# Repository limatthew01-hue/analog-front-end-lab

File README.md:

# Analog front-end lab

A simulation of a low-voltage sensor input: a 10 kΩ / 10 nF RC filter, 1.65 V bias, and an ideal 12-bit ADC with a 3.3 V reference. The goal is to preserve a 100 Hz signal while reducing a separate 20 kHz interference tone, then examine component tolerance and quantization.

This is a completed simulation study, not a fabricated circuit or a hardware measurement. Python provides the equations, waveforms, tolerance study, and ADC model. ngspice independently checks the RC response.

## Run

Use Python 3.10 or newer. From the repository root:

```sh
python3 -m venv .venv
source .venv/bin/activate
python -m pip install -r requirements.txt
python -m unittest discover -s tests -v
python src/front_end.py --out results/python
```

Windows activation: `.venv\Scripts\activate`. Only NumPy and Matplotlib are required for the Python analysis.

To regenerate the committed results, also install [ngspice](https://ngspice.sourceforge.io/download.html) and make it available on PATH:

```sh
python src/front_end.py --out results --spice
```

Use `--ngspice /path/to/ngspice` if necessary. This runs AC and transient checks and returns an error if they exceed the declared tolerances. `make test`, `make run`, and `make spice` provide the same entry points.

## Nominal results

The synthetic input is 1.65 V plus a 100 mV-peak, 100 Hz sine and a 40 mV-peak, 20 kHz sine. The ADC samples at 200 ksample/s. The run lasts 30 ms; the first 10 ms are excluded from waveform error and ratio calculations.

| Quantity | Result |
| --- | ---: |
| RC cutoff | 1,591.549 Hz |
| Gain at 100 Hz | 0.998032 V/V |
| Gain at 20 kHz | 0.079327 V/V |
| Input signal/interference ratio | 7.959 dB |
| Filtered signal/interference ratio | 29.953 dB |
| Signal/total error after ideal ADC | 29.906 dB |
| ADC LSB | 805.664 µV |
| ADC reconstruction error RMS | 230.615 µV |
| Analog output range | 1.5470–1.7530 V |
| ADC clipping | 0 of 6,000 samples |

The ratio improvement is about 22 dB for these two tones. It is not broadband SNR, ENOB, or proof that the circuit is a sufficient anti-alias filter for a real ADC.

The open markers are ngspice AC results; the green curve is the RC equation. For the recorded ngspice 42 run, all 401 frequency points pass a relative complex-error tolerance of 1e-6. The actual maximum is approximately 9.81e-16. The transient check differs from the analytical output by at most 1.267 µV after the measurement start, below the 10 µV threshold. This agreement checks the ideal circuit model, not real component accuracy.

## Equations and ADC convention

The unloaded filter uses `H(jω) = 1 / (1 + jωRC)` and `fc = 1 / (2πRC)`. The time-domain response is the exact sine response plus its decaying initial-condition term. The capacitor begins at the 1.65 V DC bias. There is no Euler time-step approximation in the Python waveform model.

The ideal ADC has `2^12 = 4096` bins of width `3.3 / 4096 V`. Each input maps to its lower-bin code, clamped to 0–4095, and is reconstructed at the center of that bin. The nonclipped reconstruction error is bounded by half an LSB. Values below 0 V or at/above 3.3 V are flagged as clipped.

The RC resistor's ideal equilibrium thermal estimate, `sqrt(kT/C)`, is 0.644 µV RMS at 300 K. The usual uniform-error ADC estimate, `LSB/sqrt(12)`, is 232.575 µV RMS. These are analytical estimates; thermal noise is not injected into the plotted waveform, and the deterministic ADC error need not be perfectly uniform.

## Component variation

The study draws 10,000 independent component sets with uniform R ±1% and C ±5% variation, using seed 7. The 5th–95th cutoff percentiles are 1,521.85–1,666.93 Hz. Deterministic worst-case corners are 1,500.75–1,692.24 Hz. These bounds describe the chosen tolerance model, not measured production data or a confidence interval for actual devices.

## Files

- `src/front_end.py`: equations, waveform and ADC models, tolerance study, CLI, and SPICE cross-check.
- `spice/rc_ac.cir`: nominal AC netlist.
- `spice/rc_transient.cir`: nominal biased sensor and interference netlist.
- `tests/test_front_end.py`: 19 tests.
- `results/metrics.json`: exact configuration and recorded numerical results.
- `results/frequency_response.csv`: 401-point AC response.
- `results/waveforms.csv`: all 6,000 simulated ADC samples.
- `results/spice_ac_check.csv`: theory and independent SPICE values at the same frequencies.
- `results/cutoff_distribution.csv`: histogram bins for the tolerance sweep.
- `results/report.md`: generated report.

The large raw ngspice transient output is regenerated in ignored `build/`, rather than committed. To run the nominal netlists directly:

```sh
mkdir -p build
ngspice -b spice/rc_ac.cir
ngspice -b spice/rc_transient.cir
```

The generated netlists in `build/` use the current CLI parameters. The checked-in `spice/` copies use the nominal component values.

## Verification and limits

The tests check DC gain, the -3.0103 dB / -45° cutoff, high-frequency roll-off, finite-load behavior, initial conditions, the RC differential equation via an independent numerical derivative, ADC bins and half-LSB error bounds, tolerance corners, reproducible seeds, and time-domain versus frequency-domain tone ratios.

The main simulation assumes an ideal source, ideal bias, and infinite ADC input impedance. A finite resistive load changes both gain and cutoff; a real ADC's switched sampling capacitor is more complicated still. Reference noise, amplifier behavior, INL/DNL, aperture jitter, parasitics, and physical anti-alias performance are excluded. A hardware extension needs a chosen ADC, acquisition/settling analysis, real bias circuitry, and measured waveforms before making board-level claims.

## Related machine-learning project

[Sensor Signal Classifier](projects/sensor-signal-classifier/) is a separate personal project in this repository. It compares fixed rules, logistic regression, and a random forest on simulated ADC signal conditions, with device-disjoint splits and a noise stress test. Its code, setup instructions, and results are self-contained in that folder.

## Related motor-control project

[Zybo Motor Speed Controller](projects/zybo-motor-controller/) implements encoder feedback, fixed-point PI control, 20 kHz PWM, a CRC-protected serial link, and a Python operator panel. It includes a switched-PWM motor simulation, self-checking RTL tests, and a hardware wiring guide. Physical board and motor measurements are pending. This project is self-contained in its own folder.

## PCB and embedded firmware

[Dual-Channel Sensor Interface PCB](projects/sensor-interface-pcb/) contains an editable KiCad schematic and routed two-layer board, BOM, fabrication exports, netlist comparison and native DRC report. [Bare-Metal STM32 Sensor Logger](projects/bare-metal-stm32-logger/) implements timer-triggered ADC sampling, circular DMA, UART queues and CRC-protected telemetry in C. Both are prototype projects; fabrication and physical MCU testing are pending.

## References

- [Texas Instruments: low-pass filtered non-inverting amplifier](https://www.ti.com/tool/CIRCUIT060057): background on an RC input pole. This lab models the passive RC portion only, not TI's amplifier circuit.
- [ngspice documentation](https://ngspice.sourceforge.io/docs.html): AC and transient simulation and control commands.

[Matthew Li's engineering portfolio](https://matthew-li-portfolio.li-matthew01.chatgpt.site)

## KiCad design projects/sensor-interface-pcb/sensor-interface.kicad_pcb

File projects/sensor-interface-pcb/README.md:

# Dual-channel sensor interface PCB

A 60 × 40 mm, two-layer board for connecting two slow, positive voltage signals to a NUCLEO-F401RE. Each channel has a 2:1 resistor divider, an MCP6002 voltage follower, and a 10 kΩ / 1 µF output filter. The MCU stays on the Nucleo board; a four-wire harness carries power, ground and the two ADC inputs.

**Revision A is a CAD prototype.** It has not been fabricated, assembled or measured. KiCad checks and an ideal-buffer simulation are complete; they do not establish hardware performance or production readiness.

## Circuit choices

The intended input range is 0–6 V with the interface powered from regulated 3.3 V. Two 33 kΩ, 1% resistors load each input by 66 kΩ and produce half the input voltage. At 6 V, the nominal buffer input is 3.0 V. The MCP6002 runs from 3.3 V; both amplifiers are unity-gain followers. The 10 kΩ resistor isolates the amplifier from the 1 µF ADC-side capacitor. C1 is the local 100 nF bypass, and C4 adds 4.7 µF near the harness.

The nominal RC cutoff is `1 / (2π × 10000 × 1e-6) = 15.915 Hz`. This design is intended for signals below roughly 5 Hz. A single RC pole is not a guarantee of alias rejection for arbitrary interference at the 100 Hz acquisition rate.

The 1% divider corners are 0.495–0.505 V/V. Assuming R ±1% and effective C ±10%, the cutoff corners are 14.325–17.863 Hz. Actual ceramic capacitance can change with DC bias and temperature; select a part whose effective capacitance meets the design target. These calculations exclude op-amp offset/noise, ADC reference error, switched-capacitor loading and layout parasitics.

## Connection to the Nucleo

J1 is a **wired harness**, not an Arduino shield footprint. Read the pin-1 square pad and silkscreen before connecting it.

| PCB pin | Signal | NUCLEO-F401RE connection |
| --- | --- | --- |
| J1.1 | +3V3 | CN6.4, 3.3 V output |
| J1.2 | GND | CN6.6, ground |
| J1.3 | ADC0 | CN8.1, A0 / PA0 / ADC1 channel 0 |
| J1.4 | ADC1 | CN8.2, A1 / PA1 / ADC1 channel 1 |
| J2.1 / J2.2 | Input 0 / ground | External 0–6 V signal / common ground |
| J3.1 / J3.2 | Input 1 / ground | External 0–6 V signal / common ground |

Supply this board from **3.3 V**, and disconnect external signals when its power is off. There is no reverse-polarity protection, isolation or overvoltage clamp; the divider is a scaling network, not a protected industrial input.

The matching [bare-metal STM32 logger](../bare-metal-stm32-logger/) configures these ADC channels and sends CRC-protected records through the Nucleo's ST-LINK virtual COM port.

## CAD and checks

Open `sensor-interface.kicad_pro` in **KiCad 7 or newer**. The schematic embeds its symbols. The PCB embeds its footprint geometry and also references the standard KiCad footprint libraries through `fp-lib-table`. On KiCad versions with a different library environment name, set `KICAD7_FOOTPRINT_DIR` to your installed footprint directory or update that table.

Recorded KiCad 7.0.11 results:

| Check | Result |
| --- | --- |
| Physical/electrical DRC | 0 violations |
| Unconnected pads | 0 |
| Footprint errors | 0 |
| Schematic-to-board net membership | All 36 pin connections across 10 nets match |
| Layout | 0.25 mm tracks; eight 0.6 / 0.3 mm vias; four 3.2 mm mounting holes |

`results/drc.txt` is the native KiCad report. `results/verification.json` records the independent netlist comparison. **ERC was not run**: the installed KiCad 7 CLI has no ERC command. Run ERC in the schematic editor and review the schematic and footprints before ordering. Zero DRC errors do not prove the circuit works.

On a Linux KiCad installation whose Python can import `pcbnew`:

```sh
make check
make export
# Optional regeneration from design.json; this replaces manual layout edits:
make regenerate
make check
make export
```

`design.json` is the generator's component/pin manifest. `scripts/build_board.py` places standard footprints, routes both layers and fills the back ground plane. The editable `.kicad_pcb` is the board used for the recorded DRC and exports. After manual CAD edits, use `make check` and `make export`, not `make regenerate`.

## Analog model

```sh
python3 -m venv .venv
. .venv/bin/activate
python -m pip install -r requirements.txt
python scripts/analyze.py --ngspice ngspice
```

The 401-point ngspice AC check uses an **ideal voltage-controlled buffer**, not an MCP6002 device model. It agrees with the analytical divider-plus-RC response to a maximum complex error of about `1.3e-9 V/V`. See `results/analog.json`, `results/frequency.csv` and the generated plot. This validates the passive calculation only.

## Fabrication package and bring-up

`fabrication/` contains the copper, solder mask, paste, silkscreen, board outline and metric Excellon drill export. The drill file declares plated vias, plated header holes and nonplated mounting holes separately in its tool attributes. `bom.csv` lists values, ratings and footprints; select exact passive parts and check their dimensions and capacitor derating before assembly. The U1 package is SOIC-8, **MCP6002-I/SN**.

The first physical checks are still pending:

1. Run schematic ERC and review the generated fabrication layers, drill plating and component orientation.
2. Inspect for shorts, then power from a current-limited 3.3 V source with signal sources disconnected. Check U1 pins 8 and 4.
3. Apply known, common-ground DC voltages to one input at a time. Measure the divider, buffer and ADC nodes before connecting the MCU.
4. Flash the companion firmware, enter the measured ADC reference voltage, and compare stable readings against a DMM.
5. Scope a slow input step and the ADC node. Check settling, reference noise and stability with the actual selected capacitors and wiring.

## Sources

- [Microchip MCP6001/2/4 datasheet, DS20001733L](https://ww1.microchip.com/downloads/en/DeviceDoc/MCP6001-1R-1U-2-4-1-MHz-Low-Power-Op-Amp-DS20001733L.pdf): package pins, supply range and amplifier characteristics.
- [ST Nucleo-64 manual, UM1724](https://www.st.com/resource/en/user_manual/um1724-stm32-nucleo64-boards-mb1136-stmicroelectronics.pdf): F401RE connector mappings.
- [ST STM32F401RE datasheet](https://www.st.com/resource/en/datasheet/stm32f401re.pdf): ADC and device electrical characteristics.
- [KiCad library license](https://www.kicad.org/libraries/license/): standard footprint attribution and exception.

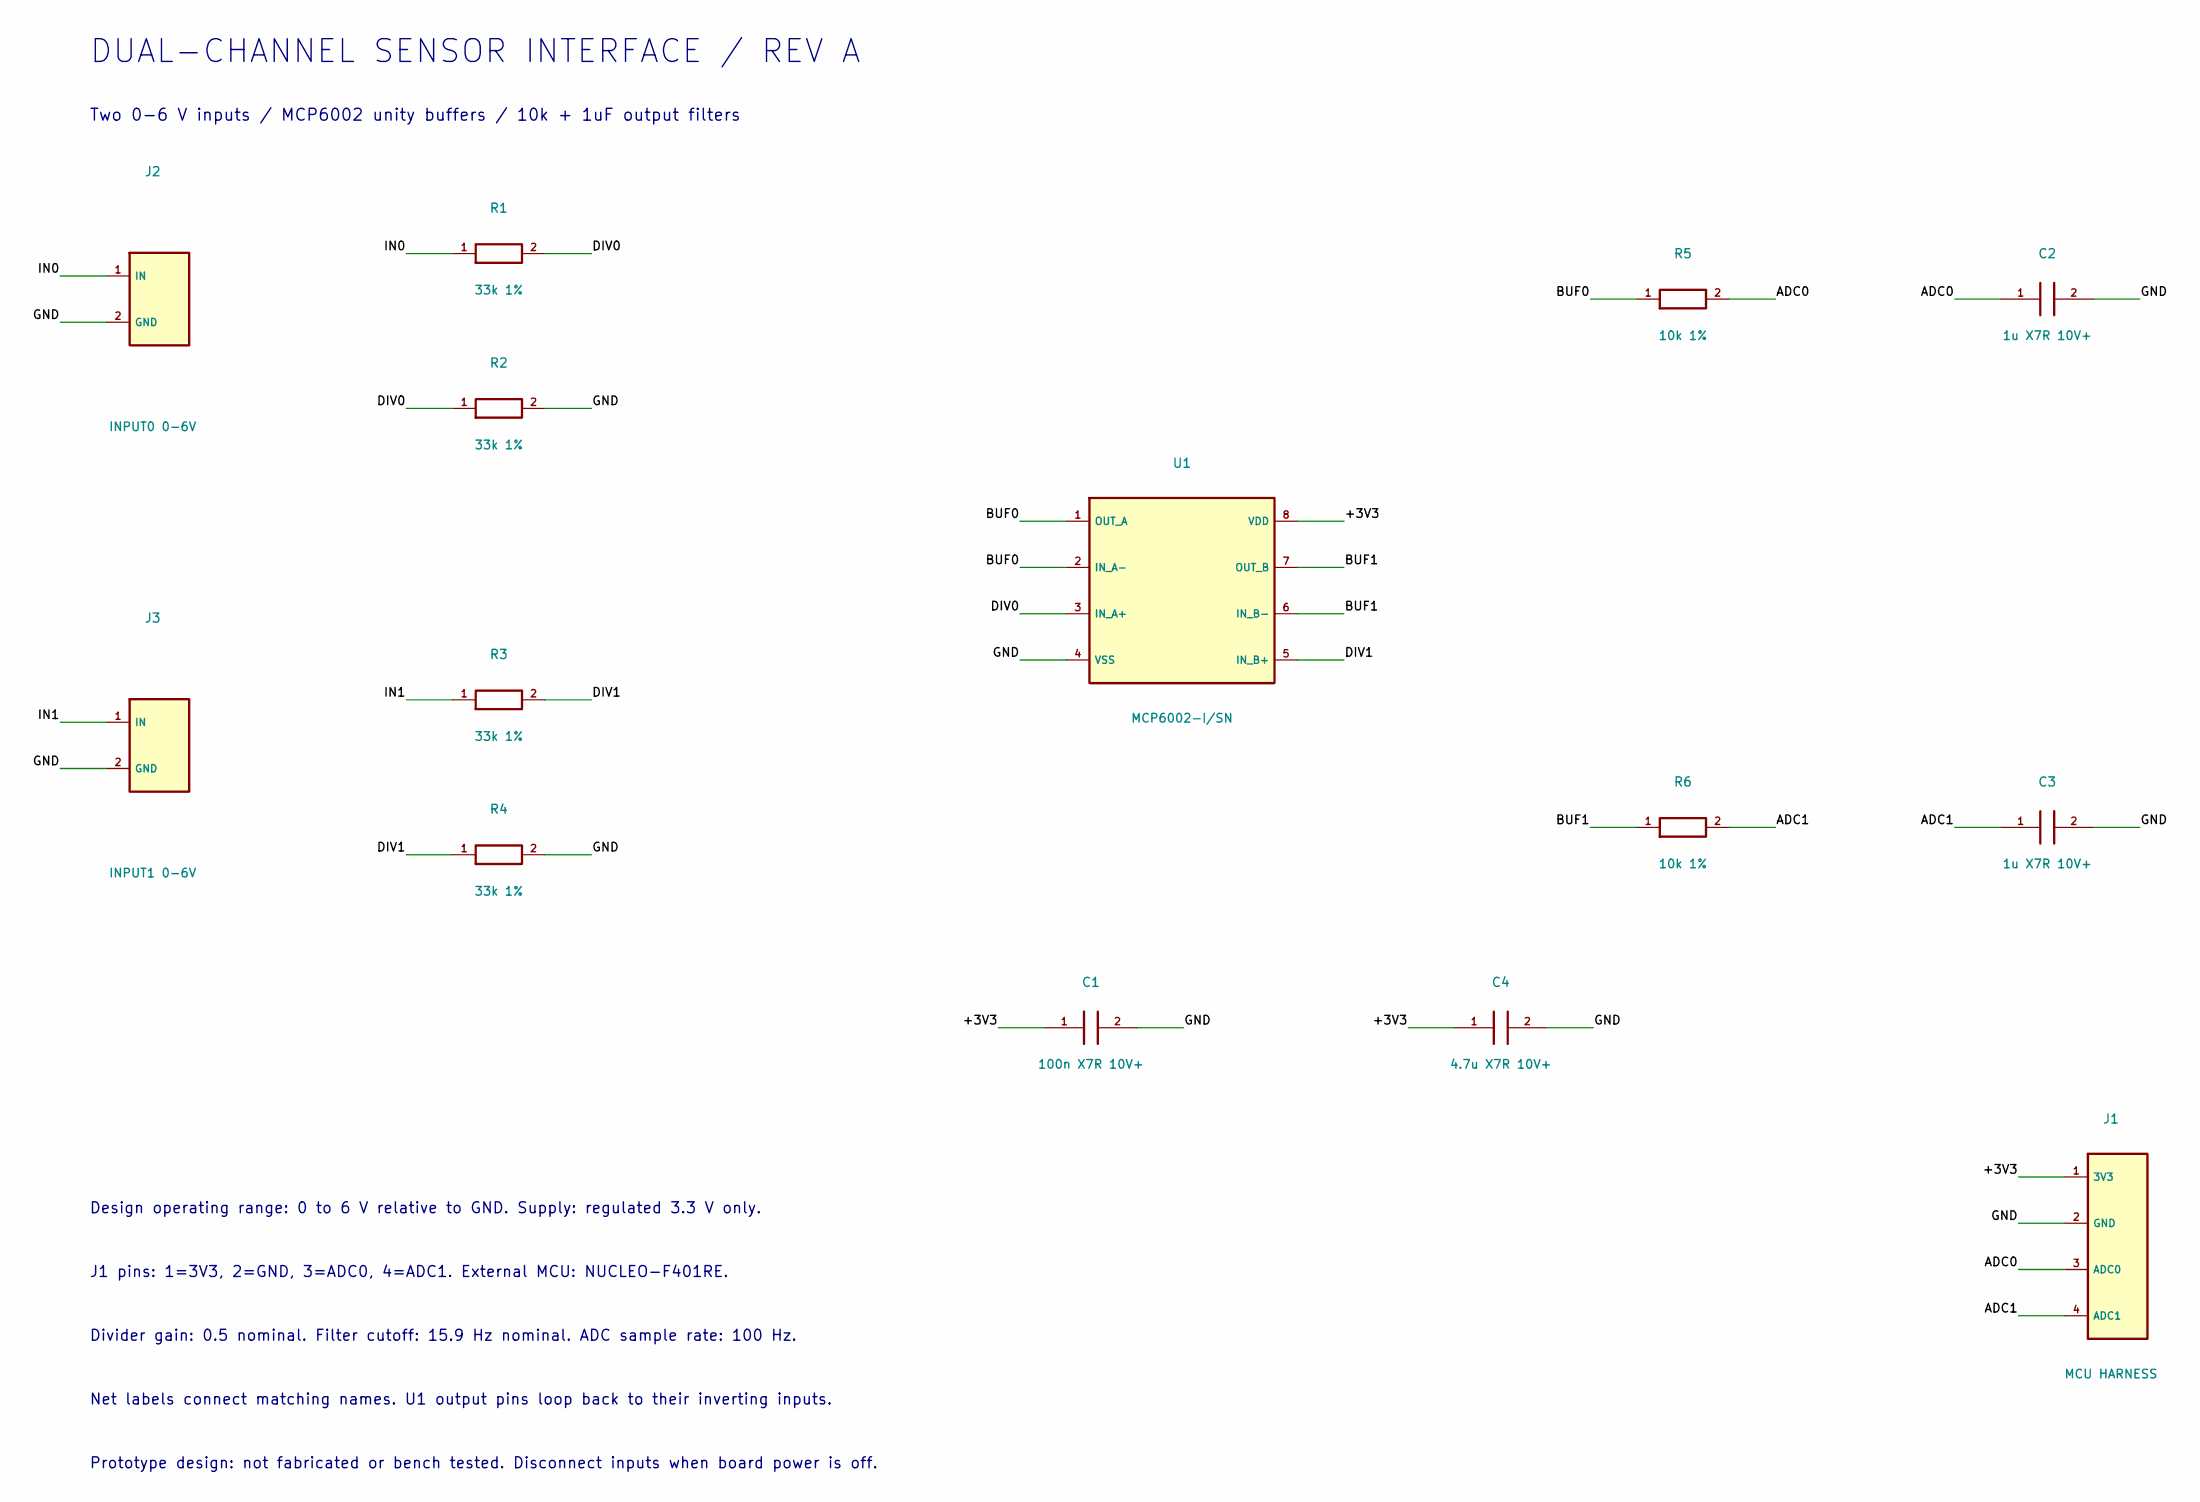
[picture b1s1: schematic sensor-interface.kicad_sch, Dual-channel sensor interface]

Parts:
C1: 100n X7R 10V+; C_0805_2012Metric
C2, C3: 1u X7R 10V+; C_0805_2012Metric
C4: 4.7u X7R 10V+; C_0805_2012Metric
J1: MCU HARNESS; PinHeader_1x04_P2.54mm_Vertical
J2: INPUT0 0-6V; PinHeader_1x02_P2.54mm_Vertical
J3: INPUT1 0-6V; PinHeader_1x02_P2.54mm_Vertical
R1, R2, R3, R4: 33k 1%; R_0805_2012Metric
R5, R6: 10k 1%; R_0805_2012Metric
U1: MCP6002-I/SN; SOIC-8_3.9x4.9mm_P1.27mm

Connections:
+3V3: C1.1, C4.1, J1.1 (3V3), U1.8 (VDD)
ADC0: C2.1, J1.3 (ADC0), R5.2
ADC1: C3.1, J1.4 (ADC1), R6.2
BUF0: R5.1, U1.1 (OUT_A), U1.2 (IN_A-)
BUF1: R6.1, U1.6 (IN_B-), U1.7 (OUT_B)
DIV0: R1.2, R2.1, U1.3 (IN_A+)
DIV1: R3.2, R4.1, U1.5 (IN_B+)
GND: C1.2, C2.2, C3.2, C4.2, J1.2 (GND), J2.2 (GND), J3.2 (GND), R2.2, R4.2, U1.4 (VSS)
IN0: J2.1 (IN), R1.1
IN1: J3.1 (IN), R3.1

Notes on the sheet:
DUAL-CHANNEL SENSOR INTERFACE / REV A
Two 0-6 V inputs / MCP6002 unity buffers / 10k + 1uF output filters
Design operating range: 0 to 6 V relative to GND. Supply: regulated 3.3 V only.
J1 pins: 1=3V3, 2=GND, 3=ADC0, 4=ADC1. External MCU: NUCLEO-F401RE.
Divider gain: 0.5 nominal. Filter cutoff: 15.9 Hz nominal. ADC sample rate: 100 Hz.
Net labels connect matching names. U1 output pins loop back to their inverting inputs.
Prototype design: not fabricated or bench tested. Disconnect inputs when board power is off.

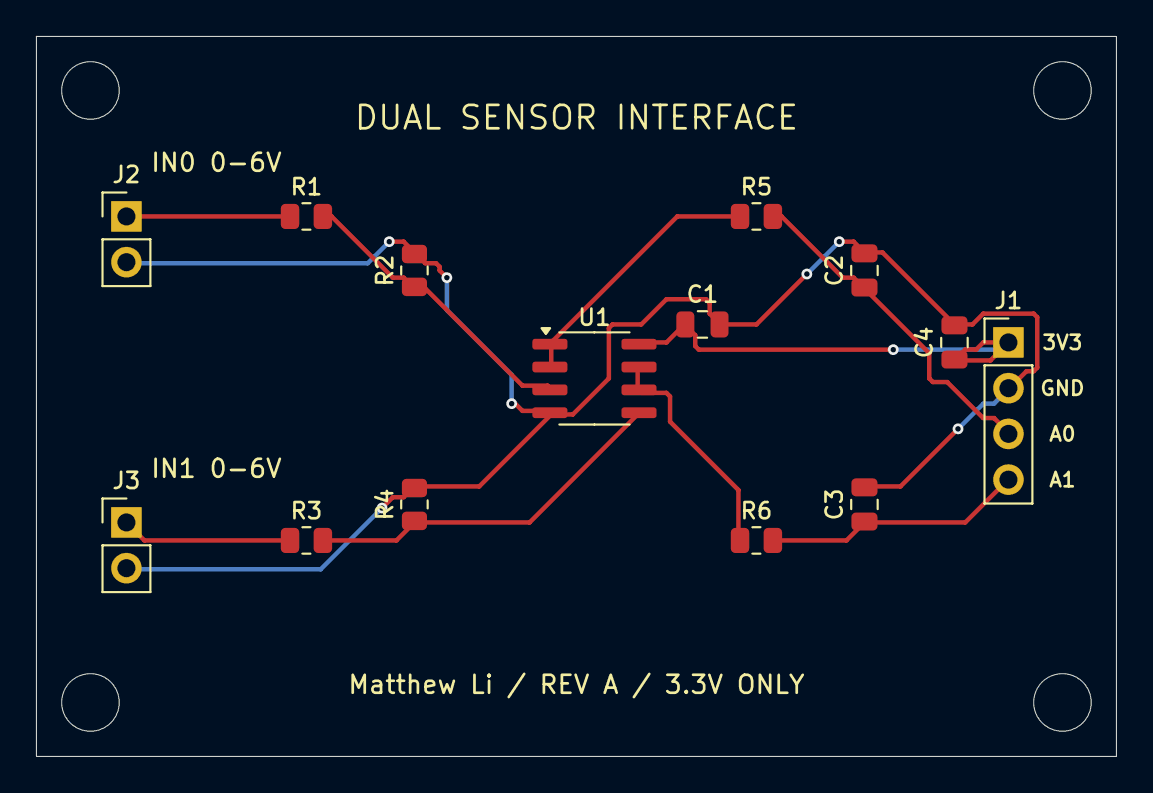
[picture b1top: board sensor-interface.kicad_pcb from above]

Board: 2 copper layers, 60.0 x 40.0 mm, 18 parts (0 on the bottom side), 10 nets.

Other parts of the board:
H1, H2, H3, H4: MountingHole_3.2mm_M3

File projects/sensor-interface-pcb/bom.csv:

Reference,Value / requirement,Footprint
J1,MCU: 3V3 / GND / A0 / A1,Connector_PinHeader_2.54mm:PinHeader_1x04_P2.54mm_Vertical
J2,INPUT0 0-6V,Connector_PinHeader_2.54mm:PinHeader_1x02_P2.54mm_Vertical
J3,INPUT1 0-6V,Connector_PinHeader_2.54mm:PinHeader_1x02_P2.54mm_Vertical
U1,MCP6002-I/SN,Package_SO:SOIC-8_3.9x4.9mm_P1.27mm
R1,33k 1%,Resistor_SMD:R_0805_2012Metric
R2,33k 1%,Resistor_SMD:R_0805_2012Metric
R3,33k 1%,Resistor_SMD:R_0805_2012Metric
R4,33k 1%,Resistor_SMD:R_0805_2012Metric
R5,10k 1%,Resistor_SMD:R_0805_2012Metric
R6,10k 1%,Resistor_SMD:R_0805_2012Metric
C1,100n X7R 10V+,Capacitor_SMD:C_0805_2012Metric
C2,1u X7R 10V+,Capacitor_SMD:C_0805_2012Metric
C3,1u X7R 10V+,Capacitor_SMD:C_0805_2012Metric
C4,4.7u X7R 10V+,Capacitor_SMD:C_0805_2012Metric
